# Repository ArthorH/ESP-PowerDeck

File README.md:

# ESP PowerDeck
Versitale development board for ESP32-S3 microcontroller

## Project Status: **Ongoing**  
**Design** ✅ — **Fabrication** ✅ — **Assembly** ✅ — **Bringup** ✅ — **Testing** ✅  
## Key technologies:
&nbsp;&nbsp;&nbsp;&nbsp; &nbsp;&nbsp;&nbsp;&nbsp; &nbsp;&nbsp;&nbsp;&nbsp; &nbsp;&nbsp;&nbsp;&nbsp;
## Who it's for

Want to play with robotics? Maybe you have a cool IoT project in mind? You don't want to hassle with assembling development modules or soldering jumper cables, and jump straight into controlling serious hardware—not just LEDs on a breadboard?

#### Power deck is for you! 
&nbsp;&nbsp;&nbsp;&nbsp; &nbsp;&nbsp;&nbsp;&nbsp;
# Features
- 60W Power delivery input
- High power 5V and 3.3V line outputs
- 3 Channel H-Bridge power output stage with "SafeMode" and to 43W single channel H-Bridge output
- I2C current feedback for H-Bridges
- WS2812 and servo otputs
- Built in UART bridge
- Built in USB 2.0 Hub for ESP32 OTG
- UVLO OVLO protection for barrel jack psu

# Block Diagram:

# Usage:
It can drive anything from simple DC motors and Steppers:

To driving bldc motors using advanced FOC alghoritms:

Also last but not least IoT projects are also possible:

# Layout:

# Author
Artem Horiunov
# License 
CERN-OHL-P V2

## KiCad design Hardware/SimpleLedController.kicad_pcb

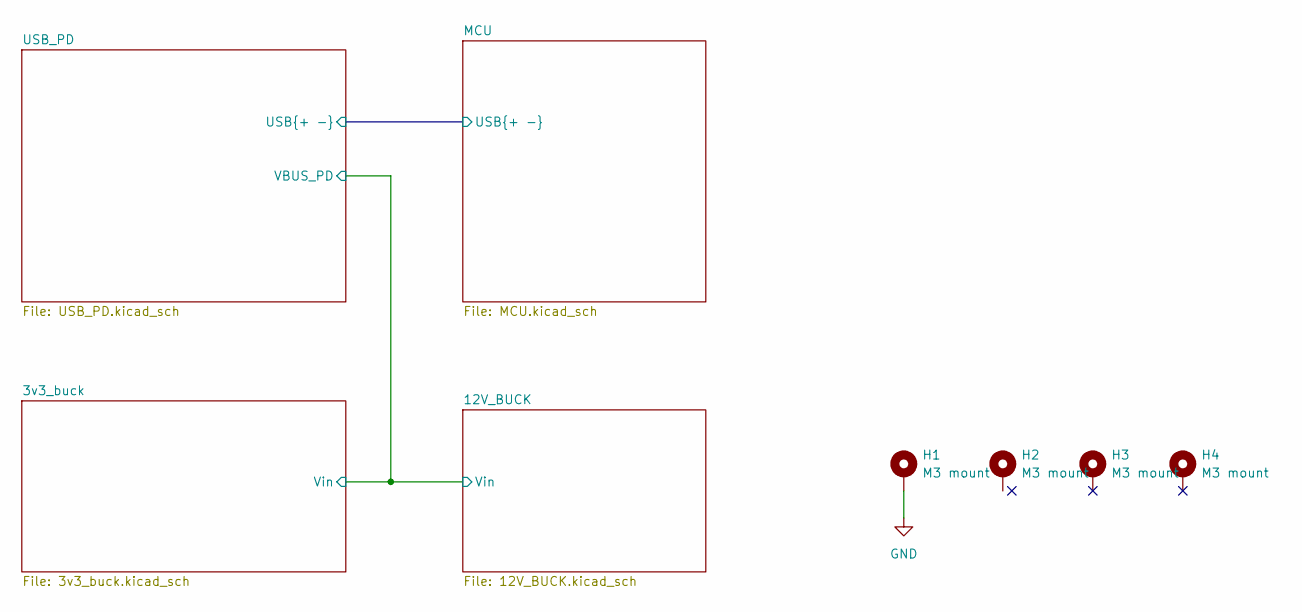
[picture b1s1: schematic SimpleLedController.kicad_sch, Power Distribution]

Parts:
H1, H2, H3, H4: M3 mount; MountingHole_3.2mm_M3_DIN965_Pad

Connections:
GND: H1.1; also elsewhere on the board

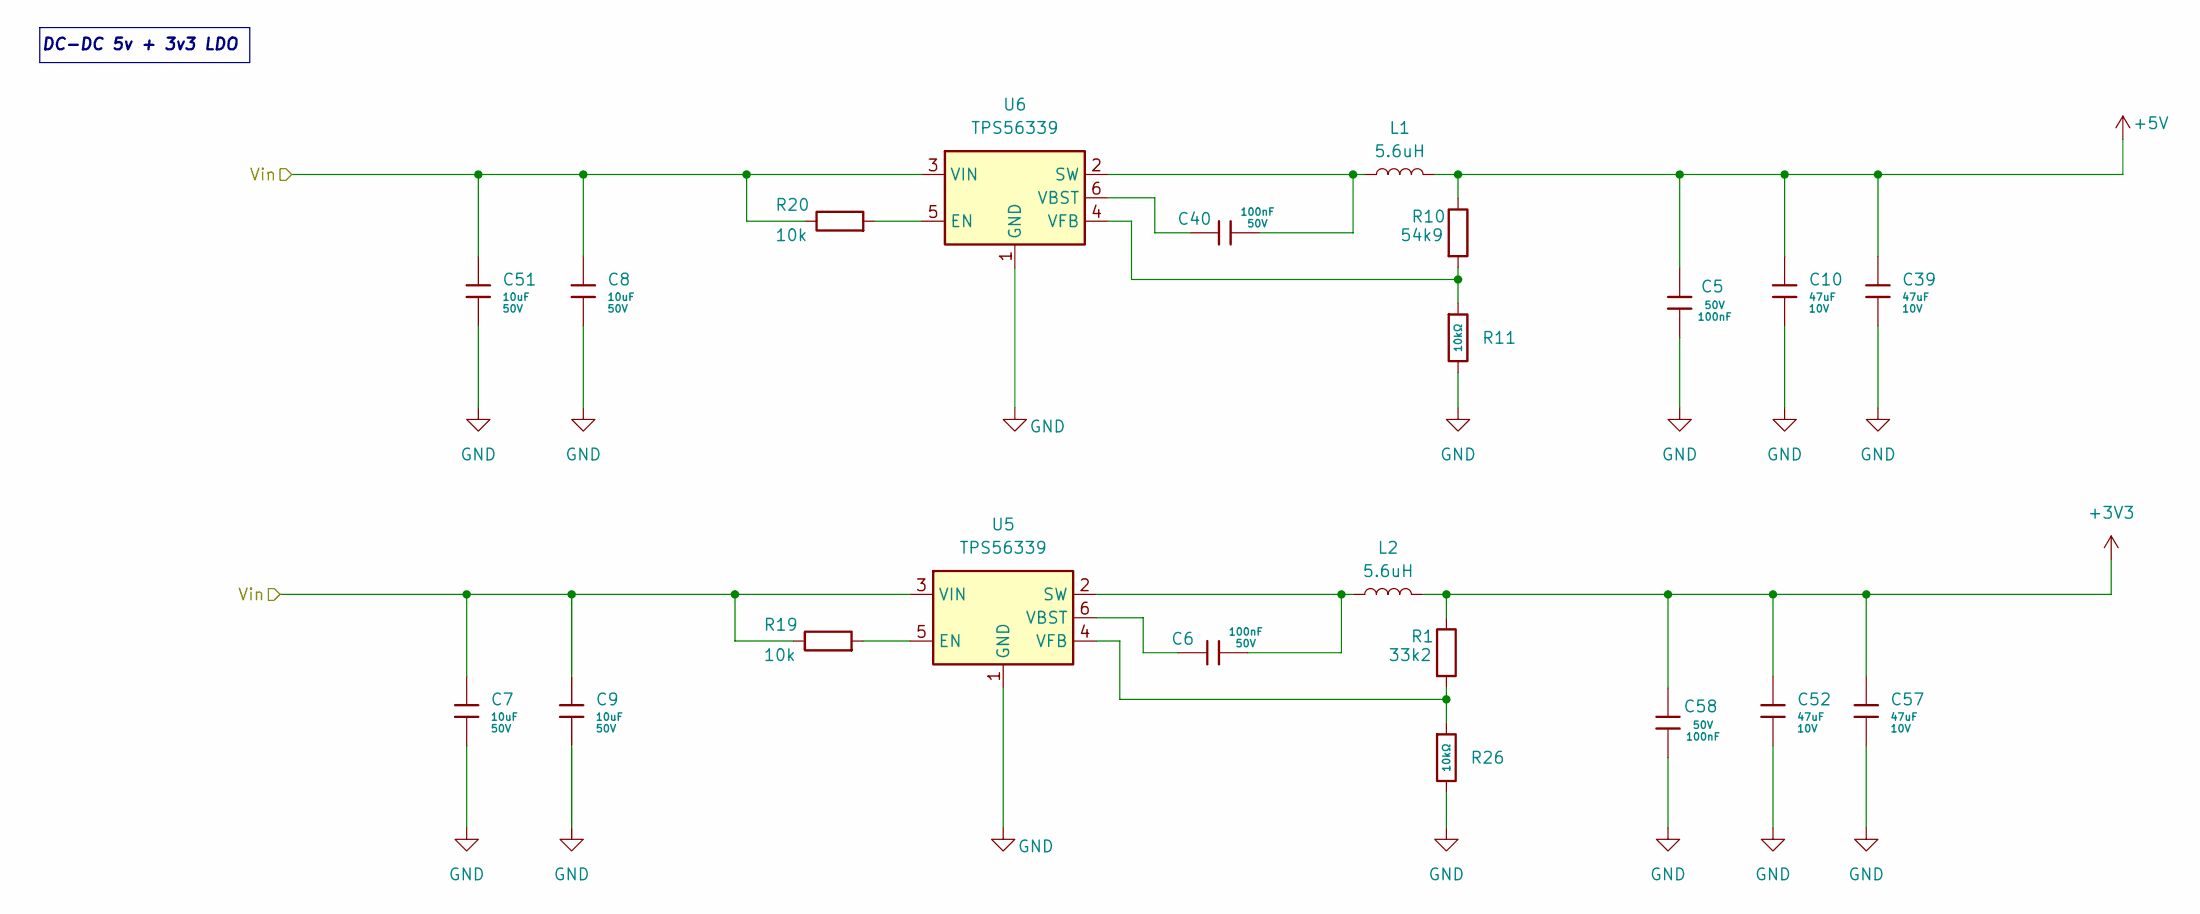
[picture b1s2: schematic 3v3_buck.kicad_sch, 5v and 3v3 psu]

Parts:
C5, C6, C40, C58: 100nF; C_0402; Voltage Rated 50V; Tolerance ±10%; Part CL05B104KB54PNC; LCSC C307331
C7, C8, C9, C51: 10uF; C_1206; Voltage Rated 50V; Tolerance ±10%; Part CL31A106KBHNNNE; LCSC C13585
C10, C39, C52, C57: 47uF; C_1206; Voltage Rated 10V; Tolerance ±20%; Part CL31A476MPHNNNE; LCSC C96123
L1, L2: 5.6uH; L_Sunlord_MWSA0518S
R1: 33k2; R_0402_1005Metric
R10: 54k9; R_0402_1005Metric
R11, R26: 10kΩ; R_0402; Overload Voltage (Max) 50V; Tolerance ±1%; Part 0402WGF1002TCE; LCSC C25744
R19, R20: 10k; R_0402_1005Metric
U5, U6: TPS56339; SOT-23-6

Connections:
+3V3: C52.1, C57.1, C58.2, L2.2, R1.1; also elsewhere on the board
+5V: C5.2, C10.1, C39.1, L1.2, R10.1; also elsewhere on the board
/USB_PD/VBUS: C7.1, C8.1, C9.1, C51.1, R19.1, R20.1, U5.3 (VIN), U6.3 (VIN); also elsewhere on the board
GND: C5.1, C7.2, C8.2, C9.2, C10.2, C39.2, C51.2, C52.2, C57.2, C58.1, R11.2, R26.2, U5.1 (GND), U6.1 (GND); also elsewhere on the board
unnamed: R19.2, U5.5 (EN)
unnamed: C6.2, L2.1, U5.2 (SW)
unnamed: C6.1, U5.6 (VBST)
unnamed: R1.2, R26.1, U5.4 (VFB)
unnamed: R20.2, U6.5 (EN)
unnamed: C40.2, L1.1, U6.2 (SW)
unnamed: C40.1, U6.6 (VBST)
unnamed: R10.2, R11.1, U6.4 (VFB)

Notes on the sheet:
DC-DC 5v + 3v3 LDO

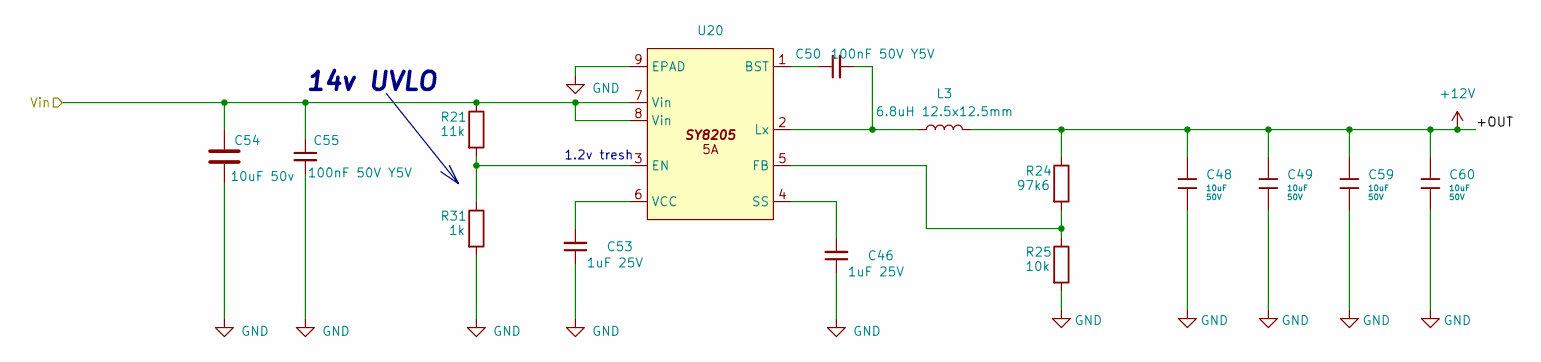
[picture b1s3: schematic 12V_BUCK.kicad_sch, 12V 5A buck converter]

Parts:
C46, C53: 1uF 25V; C_0402_1005Metric
C48, C49, C59, C60: 10uF; C_1206; Voltage Rated 50V; Tolerance ±10%; Part CL31A106KBHNNNE; LCSC C13585
C50, C55: 100nF 50V Y5V; C_0402_1005Metric
C54: 10uF 50v; C_0805_2012Metric
L3: 6.8uH 12.5x12.5mm; L_AVX_LMLP07A7; MPN YSPI0740-6R8M
R21: 11k; R_0402_1005Metric
R24: 97k6; R_0402_1005Metric
R25: 10k; R_0402_1005Metric
R31: 1k; R_0402_1005Metric
U20: Diodes_SO-8EP

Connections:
+12V: C48.1, C49.1, C59.1, C60.1, L3.2, R24.1; also elsewhere on the board
/USB_PD/VBUS: C54.1, C55.1, R21.1, U20.7 (Vin), U20.8 (Vin); also elsewhere on the board
GND: C46.1, C48.2, C49.2, C53.1, C54.2, C55.2, C59.2, C60.2, R25.2, R31.2, U20.9 (EPAD); also elsewhere on the board
unnamed: C50.1, U20.1 (BST)
unnamed: R21.2, R31.1, U20.3 (EN)
unnamed: R24.2, R25.1, U20.5 (FB)
unnamed: C50.2, L3.1, U20.2 (Lx)
unnamed: C46.2, U20.4 (SS)
unnamed: C53.2, U20.6 (VCC)

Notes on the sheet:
14v UVLO
1.2v tresh

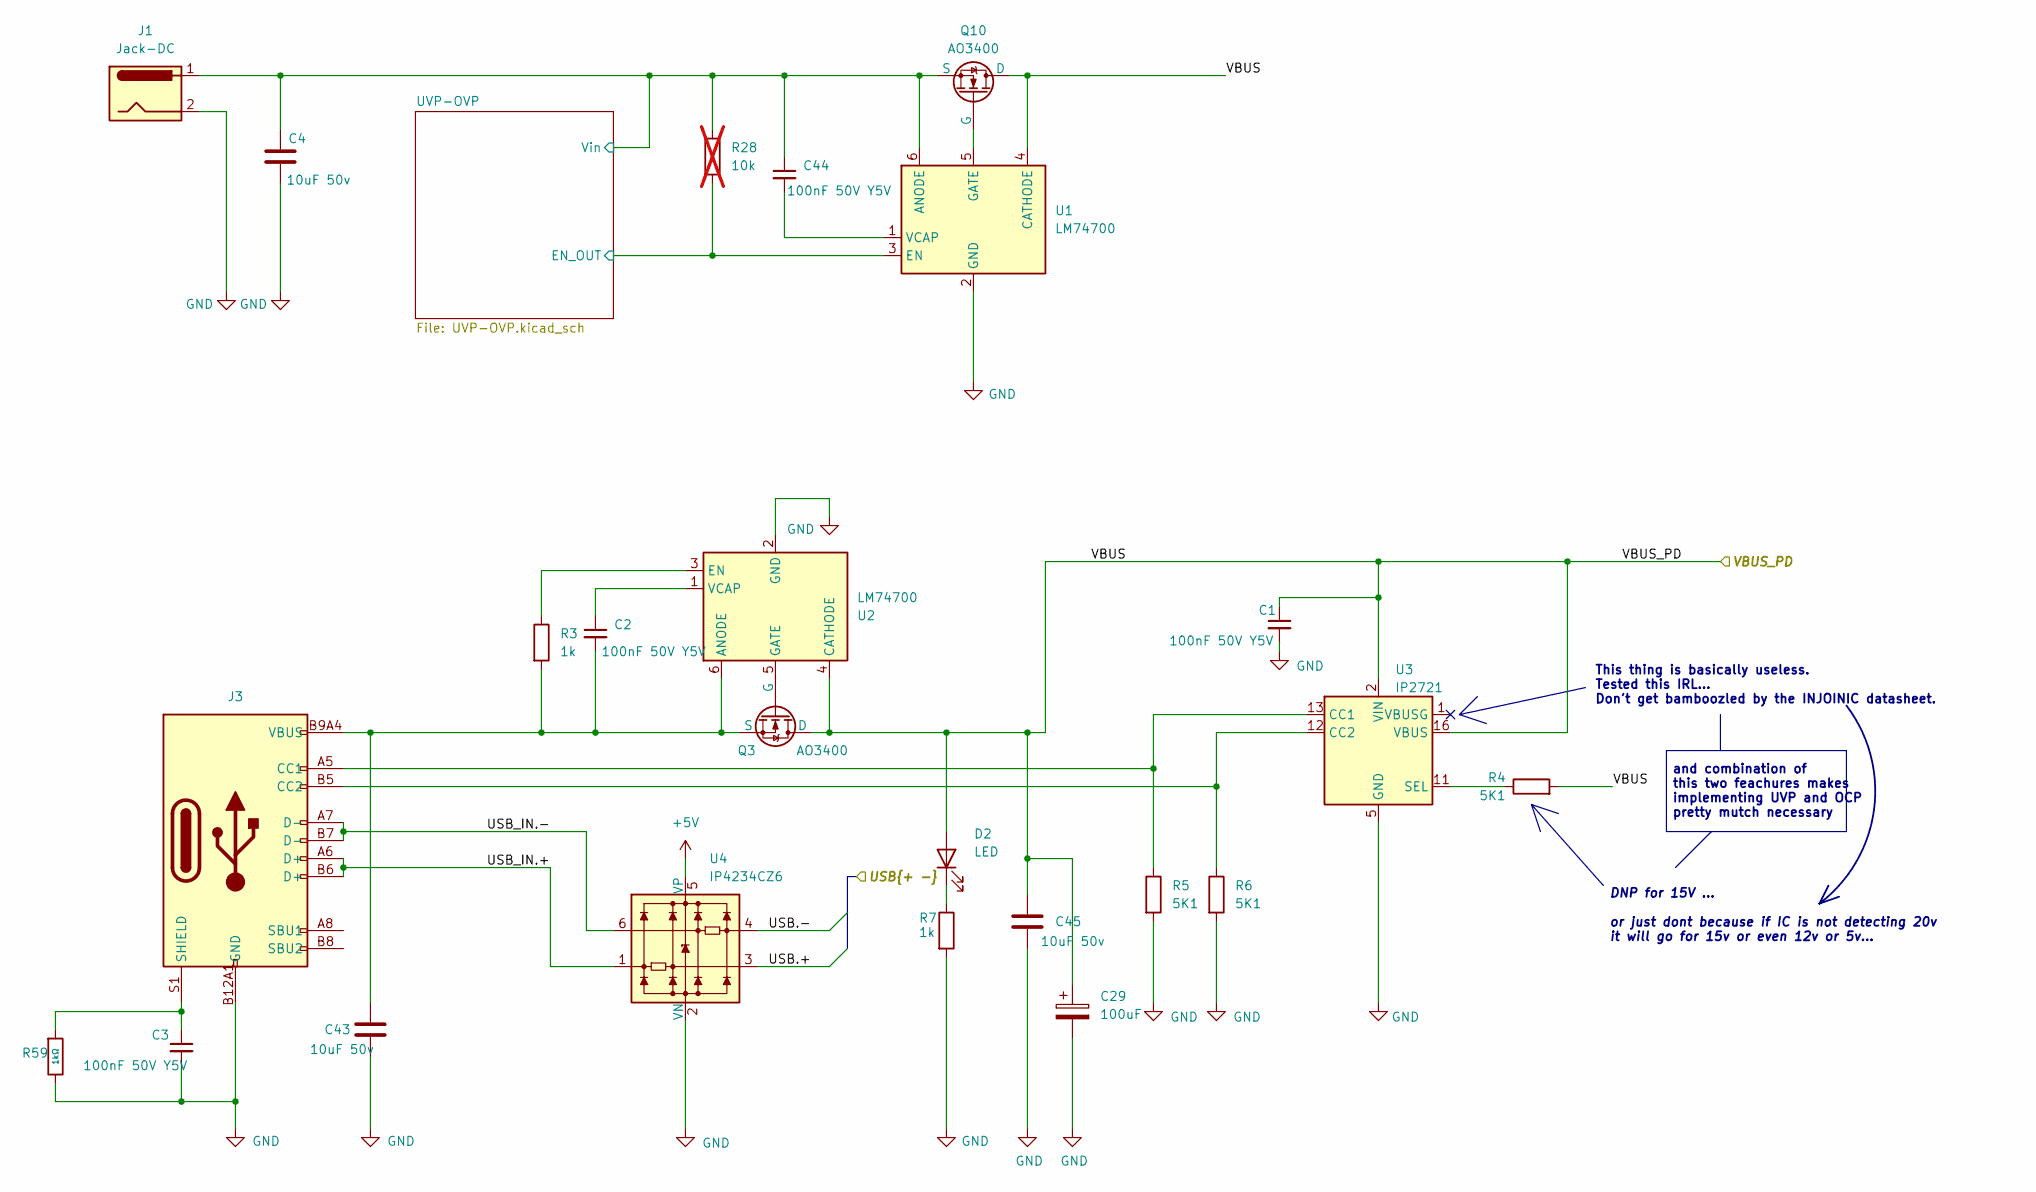
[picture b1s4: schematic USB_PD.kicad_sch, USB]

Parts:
C1, C2, C3, C44: 100nF 50V Y5V; C_0402_1005Metric
C4, C43, C45: 10uF 50v; C_0805_2012Metric
C29: 100uF; CP_Elec_6.3x5.4
D2: LED; D_0603_1608Metric
J1: Jack-DC; BarrelJack_Kycon_KLDX-0202-xC_Horizontal
J3: Connector, USB-TYPE-C-16P; TYPE-C-SMD_HX-TYPE-C-16PIN; LCSC C2927039
Q3, Q10: AO3400; SOT-23
R3, R7: 1k; R_0402_1005Metric
R4, R5, R6: 5K1; R_0402_1005Metric
R28: 10k; R_0402_1005Metric; not fitted
R59: 1kΩ; R_0402; Overload Voltage (Max) 50V; Tolerance ±1%; Part 0402WGF1001TCE; LCSC C11702
U1, U2: LM74700; SOT-23-6
U3: IP2721; TSSOP-16_4.4x5mm_P0.65mm
U4: IP4234CZ6; SC-74-6_1.55x2.9mm_P0.95mm

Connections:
+5V: U4.5 (VP); also elsewhere on the board
/MCU/USB.+: U4.3; also elsewhere on the board
/MCU/USB.-: U4.4; also elsewhere on the board
/USB_PD/USB_IN.+: J3.A6 (D+), J3.B6 (D+), U4.1
/USB_PD/USB_IN.-: J3.A7 (D-), J3.B7 (D-), U4.6
/USB_PD/UVP-OVP/EN_OUT: R28.2, U1.3 (EN); also elsewhere on the board
/USB_PD/UVP-OVP/Vin: C4.1, C44.1, J1.1, Q10.3 (S), R28.1, U1.6 (ANODE); also elsewhere on the board
/USB_PD/VBUS: C1.1, C29.1, C45.1, D2.2 (A), Q3.2 (D), Q10.2 (D), R4.2, U1.4 (CATHODE), U2.4 (CATHODE), U3.2 (VIN), U3.16 (VBUS); also elsewhere on the board
GND: C1.2, C3.2, C4.2, C29.2, C43.2, C45.2, J1.2, J3.A12B1 (GND), J3.B12A1 (GND), R5.2, R6.2, R7.2, R59.2, U1.2 (GND), U2.2 (GND), U3.5 (GND), U4.2 (VN); also elsewhere on the board
unnamed: D2.1 (K), R7.1
unnamed: J3.A5 (CC1), R5.1, U3.13 (CC1)
unnamed: J3.B5 (CC2), R6.1, U3.12 (CC2)
unnamed: C3.1, J3.S1 (SHIELD), R59.1
unnamed: Q3.1 (G), U2.5 (GATE)
unnamed: C2.2, C43.1, J3.A9B4 (VBUS), J3.B9A4 (VBUS), Q3.3 (S), R3.2, U2.6 (ANODE)
unnamed: Q10.1 (G), U1.5 (GATE)
unnamed: C44.2, U1.1 (VCAP)
unnamed: R3.1, U2.3 (EN)
unnamed: C2.1, U2.1 (VCAP)
unnamed: R4.1, U3.11 (SEL)

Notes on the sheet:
and combination of this two feachures makes implementing UVP and OCP pretty mutch necessary
DNP for 15V ... or just dont because if IC is not detecting 20v it will go for 15v or even 12v or 5v...
This thing is basically useless. Tested this IRL... Don't get bamboozled by the INJOINIC datasheet.

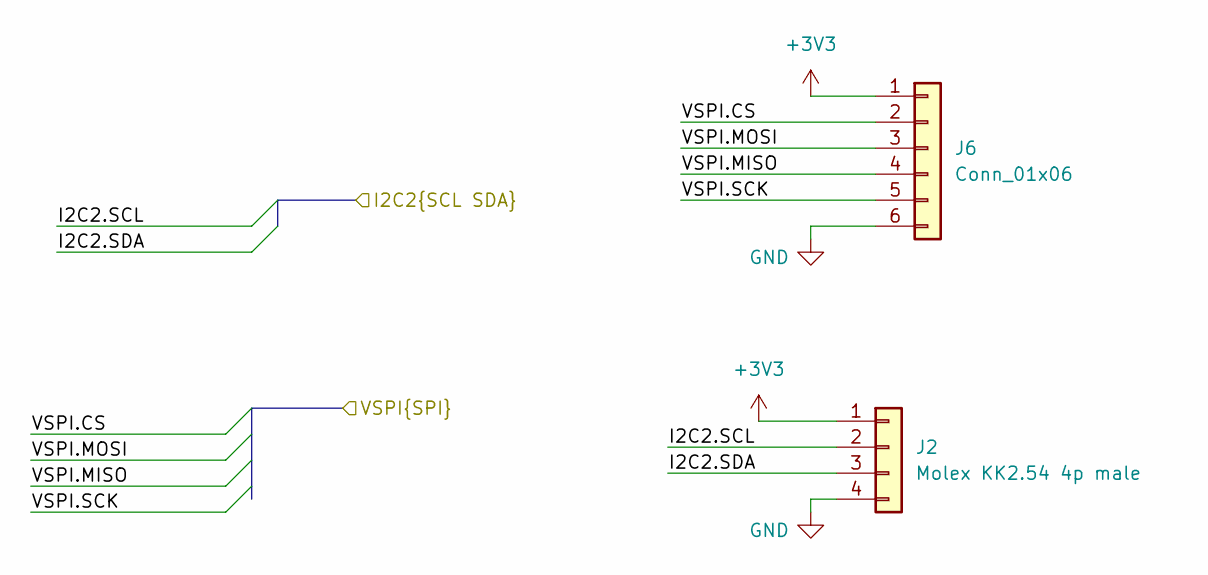
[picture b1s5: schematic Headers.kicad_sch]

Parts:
J2: Molex KK2.54 4p male; JST_GH_BM04B-GHS-TBT_1x04-1MP_P1.25mm_Vertical
J6: Conn_01x06; JST_GH_BM06B-GHS-TBT_1x06-1MP_P1.25mm_Vertical

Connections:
+3V3: J2.1, J6.1; also elsewhere on the board
/MCU/ESP32S3/I2C2.SCL: J2.2; also elsewhere on the board
/MCU/ESP32S3/I2C2.SDA: J2.3; also elsewhere on the board
/MCU/ESP32S3/VSPI.CS: J6.2; also elsewhere on the board
/MCU/ESP32S3/VSPI.MISO: J6.4; also elsewhere on the board
/MCU/ESP32S3/VSPI.MOSI: J6.3; also elsewhere on the board
/MCU/ESP32S3/VSPI.SCK: J6.5; also elsewhere on the board
GND: J2.4, J6.6; also elsewhere on the board

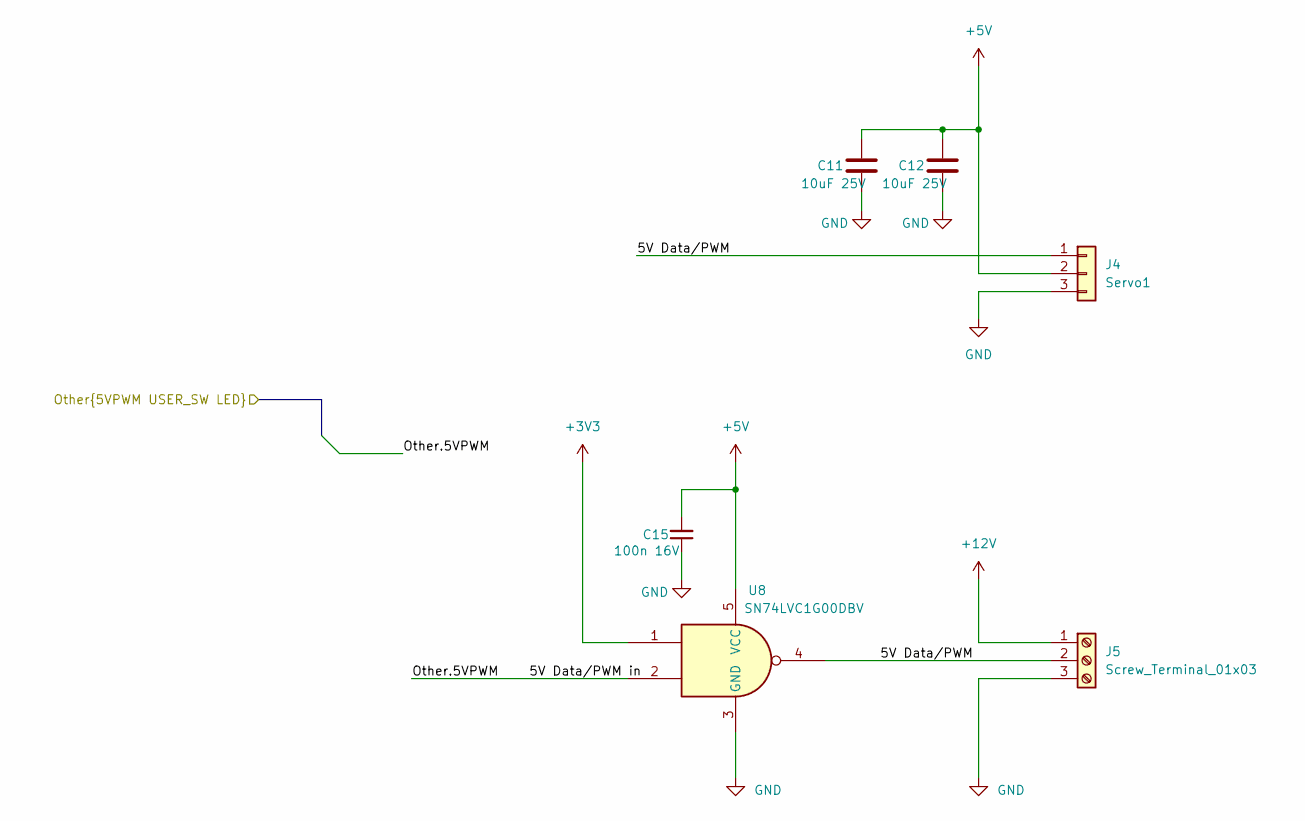
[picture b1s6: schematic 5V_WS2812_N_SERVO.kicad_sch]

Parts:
C11, C12: 10uF 25V; R_0402_1005Metric
C15: 100n 16V; C_0402_1005Metric
J4: Servo1; PinHeader_1x03_P2.54mm_Vertical_SMD_Pin1Left
J5: Screw_Terminal_01x03; TerminalBlock_Altech_AK300-3_P5.00mm
U8: SN74LVC1G00DBV; SOT-23-5

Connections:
+3V3: U8.1; also elsewhere on the board
+5V: C11.1, C12.1, C15.2, J4.2, U8.5 (VCC); also elsewhere on the board
+12V: J5.1; also elsewhere on the board
/MCU/5V WS2812 and Servo/5V Data/PWM: J4.1, J5.2, U8.4
/MCU/5V WS2812 and Servo/Other.5VPWM: U8.2; also elsewhere on the board
GND: C11.2, C12.2, C15.1, J4.3, J5.3, U8.3 (GND); also elsewhere on the board

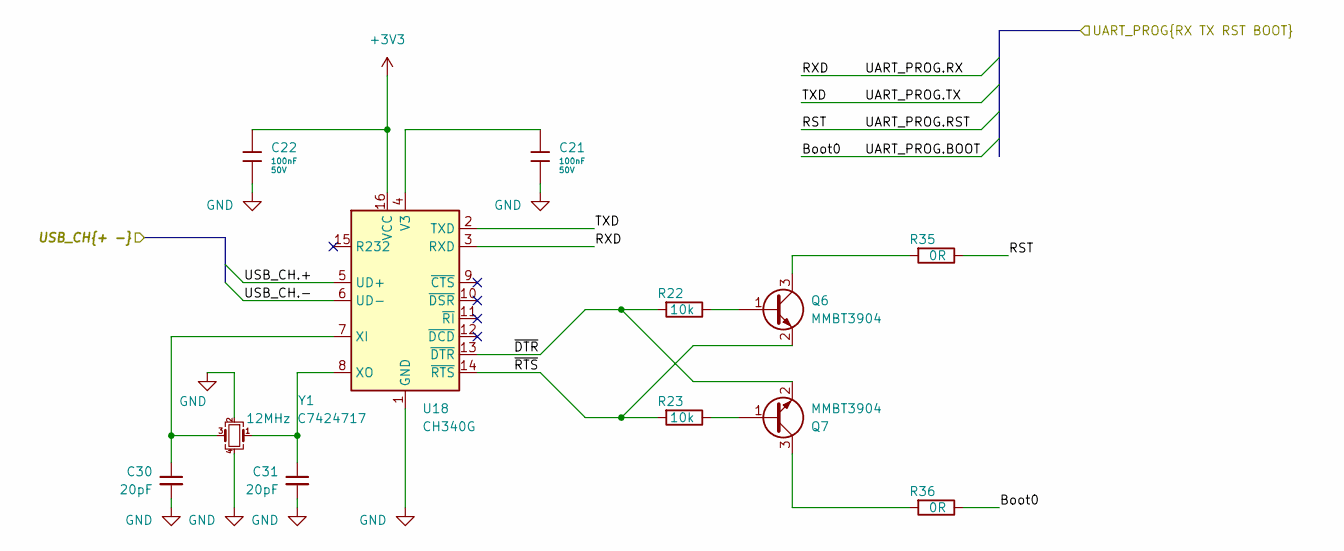
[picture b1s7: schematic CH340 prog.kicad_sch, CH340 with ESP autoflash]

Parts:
C21, C22: 100nF; C_0402; Voltage Rated 50V; Tolerance ±10%; Part CL05B104KB54PNC; LCSC C307331
C30, C31: 20pF; C_0402_1005Metric
Q6, Q7: MMBT3904; SOT-23
R22, R23: 10k; R_0402_1005Metric
R35, R36: 0R; R_0402_1005Metric
U18: CH340G; SOIC-16_3.9x9.9mm_P1.27mm
Y1: 12MHz C7424717; Crystal_SMD_3225-4Pin_3.2x2.5mm

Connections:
+3V3: C22.1, U18.16 (VCC); also elsewhere on the board
/MCU/CH340 prog/UART_PROG.BOOT: R36.1; also elsewhere on the board
/MCU/CH340 prog/UART_PROG.RST: R35.1; also elsewhere on the board
/MCU/CH340 prog/UART_PROG.RX: U18.3 (RXD); also elsewhere on the board
/MCU/CH340 prog/UART_PROG.TX: U18.2 (TXD); also elsewhere on the board
/MCU/CH340 prog/USB_CH.+: U18.5 (UD+); also elsewhere on the board
/MCU/CH340 prog/USB_CH.-: U18.6 (UD-); also elsewhere on the board
/MCU/CH340 prog/~DTR: Q7.2 (E), R22.2, U18.13 (~DTR)
/MCU/CH340 prog/~RTS: Q6.2 (E), R23.2, U18.14 (~RTS)
GND: C21.2, C22.2, C30.2, C31.2, U18.1 (GND), Y1.2, Y1.4; also elsewhere on the board
unnamed: Q6.1 (B), R22.1
unnamed: Q6.3 (C), R35.2
unnamed: Q7.1 (B), R23.1
unnamed: Q7.3 (C), R36.2
unnamed: C21.1, U18.4 (V3)
unnamed: C30.1, U18.7 (XI), Y1.3
unnamed: C31.1, U18.8 (XO), Y1.1

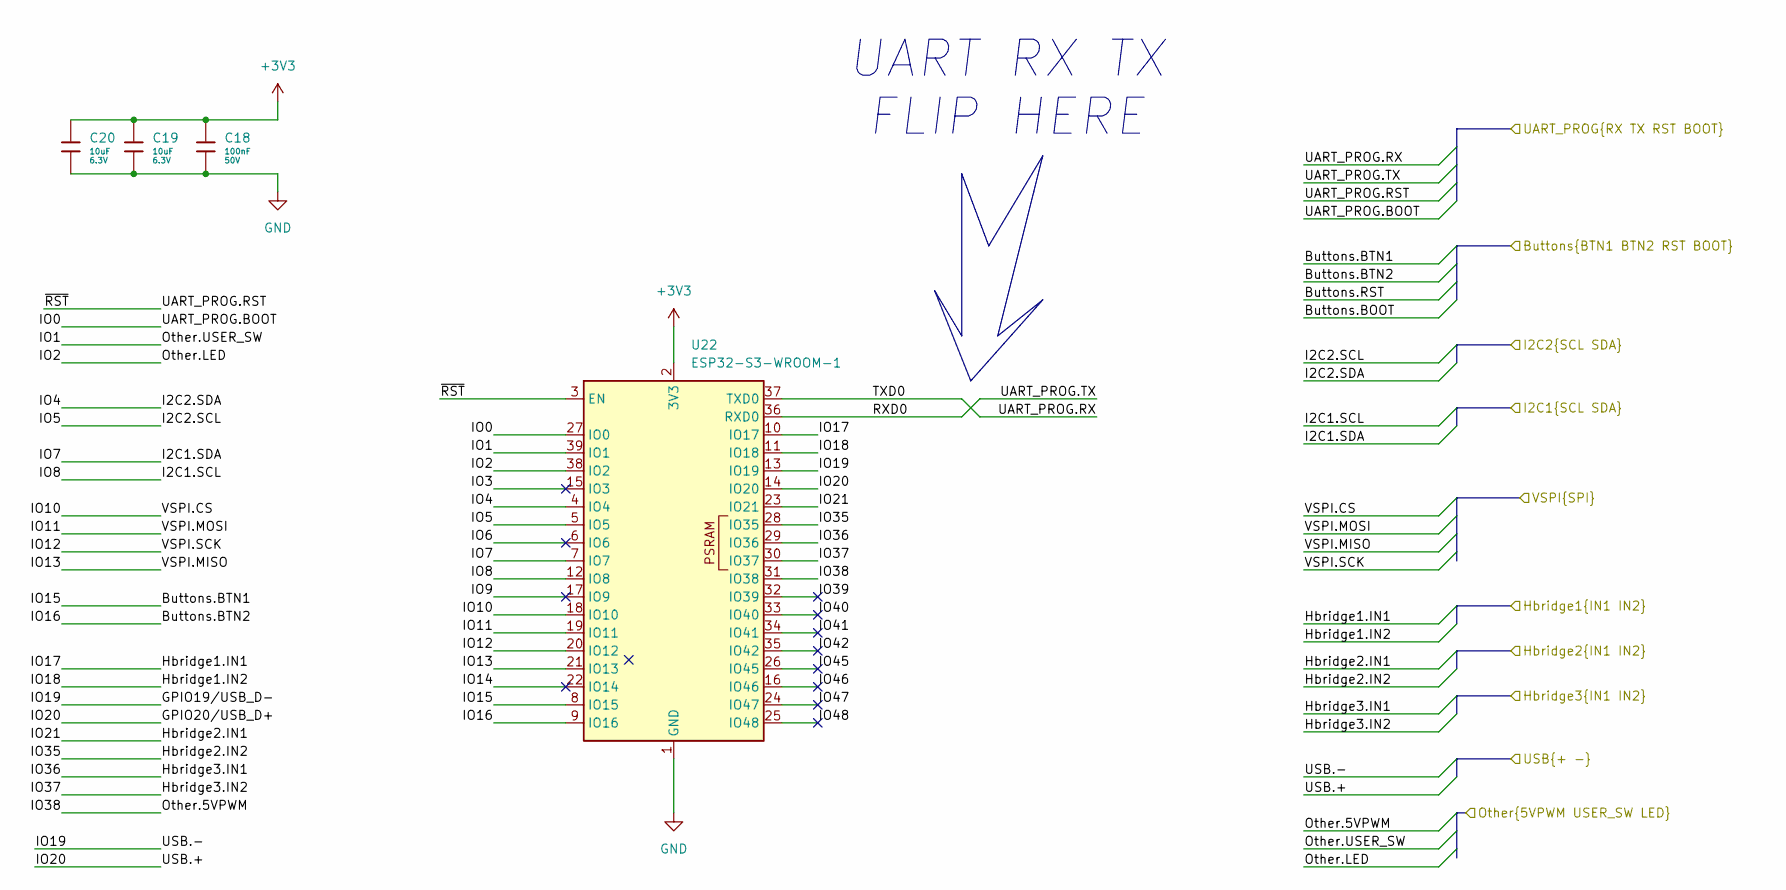
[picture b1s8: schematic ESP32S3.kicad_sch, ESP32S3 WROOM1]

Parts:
C18: 100nF; C_0402; Voltage Rated 50V; Tolerance ±10%; Part CL05B104KB54PNC; LCSC C307331
C19, C20: 10uF; C_0402; Voltage Rated 6.3V; Tolerance ±20%; Part CL05A106MQ5NUNC; LCSC C15525
U22: ESP32-S3-WROOM-1

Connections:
+3V3: C18.1, C19.1, C20.1, U22.2 (3V3); also elsewhere on the board
/MCU/5V WS2812 and Servo/Other.5VPWM: U22.31 (IO38); also elsewhere on the board
/MCU/5V WS2812 and Servo/Other.LED: U22.38 (IO2); also elsewhere on the board
/MCU/5V WS2812 and Servo/Other.USER_SW: U22.39 (IO1); also elsewhere on the board
/MCU/Buttons/Buttons.BTN1: U22.8 (IO15); also elsewhere on the board
/MCU/Buttons/Buttons.BTN2: U22.9 (IO16)
/MCU/CH340 prog/UART_PROG.BOOT: U22.27 (IO0); also elsewhere on the board
/MCU/CH340 prog/UART_PROG.RST: U22.3 (EN); also elsewhere on the board
/MCU/CH340 prog/UART_PROG.RX: U22.37 (TXD0); also elsewhere on the board
/MCU/CH340 prog/UART_PROG.TX: U22.36 (RXD0); also elsewhere on the board
/MCU/ESP32S3/Hbridge1.IN1: U22.10 (IO17); also elsewhere on the board
/MCU/ESP32S3/Hbridge1.IN2: U22.11 (IO18); also elsewhere on the board
/MCU/ESP32S3/Hbridge2.IN1: U22.23 (IO21); also elsewhere on the board
/MCU/ESP32S3/Hbridge2.IN2: U22.28 (IO35); also elsewhere on the board
/MCU/ESP32S3/Hbridge3.IN1: U22.29 (IO36); also elsewhere on the board
/MCU/ESP32S3/Hbridge3.IN2: U22.30 (IO37); also elsewhere on the board
/MCU/ESP32S3/I2C1.SCL: U22.12 (IO8); also elsewhere on the board
/MCU/ESP32S3/I2C1.SDA: U22.7 (IO7); also elsewhere on the board
/MCU/ESP32S3/I2C2.SCL: U22.5 (IO5); also elsewhere on the board
/MCU/ESP32S3/I2C2.SDA: U22.4 (IO4); also elsewhere on the board
/MCU/ESP32S3/IO3: U22.15 (IO3)
/MCU/ESP32S3/IO6: U22.6 (IO6)
/MCU/ESP32S3/IO9: U22.17 (IO9)
/MCU/ESP32S3/IO14: U22.22 (IO14)
/MCU/ESP32S3/IO39: U22.32 (IO39)
/MCU/ESP32S3/IO40: U22.33 (IO40)
/MCU/ESP32S3/IO41: U22.34 (IO41)
/MCU/ESP32S3/IO42: U22.35 (IO42)
/MCU/ESP32S3/IO45: U22.26 (IO45)
/MCU/ESP32S3/IO46: U22.16 (IO46)
/MCU/ESP32S3/IO47: U22.24 (IO47)
/MCU/ESP32S3/IO48: U22.25 (IO48)
/MCU/ESP32S3/USB.+: U22.14 (IO20); also elsewhere on the board
/MCU/ESP32S3/USB.-: U22.13 (IO19); also elsewhere on the board
/MCU/ESP32S3/VSPI.CS: U22.18 (IO10); also elsewhere on the board
/MCU/ESP32S3/VSPI.MISO: U22.21 (IO13); also elsewhere on the board
/MCU/ESP32S3/VSPI.MOSI: U22.19 (IO11); also elsewhere on the board
/MCU/ESP32S3/VSPI.SCK: U22.20 (IO12); also elsewhere on the board
GND: C18.2, C19.2, C20.2, U22.1 (GND), U22.40 (GND), U22.41 (GND); also elsewhere on the board

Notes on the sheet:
UART RX TX FLIP HERE

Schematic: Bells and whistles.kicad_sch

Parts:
D3: Red; D_0603; Part KT-0603R; LCSC C2286
R8: 1kΩ; R_0402; Overload Voltage (Max) 50V; Tolerance ±1%; Part 0402WGF1001TCE; LCSC C11702

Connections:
/MCU/5V WS2812 and Servo/Other.LED: D3.2; also elsewhere on the board
GND: R8.2; also elsewhere on the board
unnamed: D3.1, R8.1

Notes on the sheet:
buzz with PWM on engines if you will
buzzer is no more

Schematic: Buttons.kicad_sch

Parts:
C13, C16, C17: 100n 16V; C_0402_1005Metric
R9, R15, R16: 10k; R_0402_1005Metric
R13, R17, R18: 100R; R_0402_1005Metric
SW1, SW3, SW4: RESET; SW_Tactile_SPST_NO_Straight_CK_PTS636Sx25SMTRLFS; MPN TSB008A2530A; LCSC C2888954

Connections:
+3V3: R9.1, R15.1, R16.1; also elsewhere on the board
/MCU/Buttons/Buttons.BOOT: C16.2, R15.2, R17.1
/MCU/Buttons/Buttons.BTN1: C13.2, R9.2, R13.1; also elsewhere on the board
/MCU/Buttons/Buttons.RST: C17.2, R16.2, R18.1
GND: C13.1, C16.1, C17.1, SW1.2, SW3.2, SW4.2; also elsewhere on the board
unnamed: R13.2, SW1.1
unnamed: R17.2, SW3.1
unnamed: R18.2, SW4.1

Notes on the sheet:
USER button2 is no more use WIFI :)
Note: if autoflash works as intended then remove boot 1 and replace as user btn

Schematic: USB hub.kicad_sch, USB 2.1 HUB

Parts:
C32, C33: 10uF 6.3V; C_0603_1608Metric
U19: SL2.1A; SO-16_3.9x9.9mm_P1.27mm
Y2: 12MHz C7424717; Crystal_SMD_3225-4Pin_3.2x2.5mm

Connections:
+5V: U19.11 (VDD5); also elsewhere on the board
/MCU/CH340 prog/USB_CH.+: U19.8 (DP1); also elsewhere on the board
/MCU/CH340 prog/USB_CH.-: U19.7 (DM1); also elsewhere on the board
/MCU/ESP32S3/USB.+: U19.6 (DP2); also elsewhere on the board
/MCU/ESP32S3/USB.-: U19.5 (DM2); also elsewhere on the board
/MCU/USB.+: U19.10 (DP); also elsewhere on the board
/MCU/USB.-: U19.9 (DM); also elsewhere on the board
GND: C32.1, C33.1, U19.12 (GND), Y2.2, Y2.4; also elsewhere on the board
unnamed: C32.2, U19.14 (VDD18)
unnamed: C33.2, U19.13 (VDD33)
unnamed: U19.16 (XIN), Y2.3
unnamed: U19.15 (XOUT), Y2.1

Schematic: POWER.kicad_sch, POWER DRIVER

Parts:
D1: LED; LED_0603_1608Metric
R12: 10kΩ; R_0402; Overload Voltage (Max) 50V; Tolerance ±1%; Part 0402WGF1002TCE; LCSC C25744
R47: 10k; R_0402_1005Metric
R48: 680R; R_0402_1005Metric
S1: DIP Switch x 2; SW-SMD_218-2LPSTRF; Current Rating 25mA; Voltage Rating 24V; Part 218-2LPSTR; LCSC C2961921

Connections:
+3V3: S1.3, S1.4; also elsewhere on the board
/MCU/5V WS2812 and Servo/Other.USER_SW: R12.1, S1.1; also elsewhere on the board
/MCU/POWER SECTION/DRV1/~SAFE OPERATION: D1.2 (A), R47.1, S1.2; also elsewhere on the board
GND: R12.2, R47.2, R48.2; also elsewhere on the board
unnamed: D1.1 (K), R48.1

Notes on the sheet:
SAFE MODE OFF

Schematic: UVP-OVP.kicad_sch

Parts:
D4: 14v; D_SOD-123
Q4: MMBT3906; SOT-23
Q5, Q9: MMBT3904; SOT-23
R39: 1k5; R_0402_1005Metric
R40: 39k; R_0402_1005Metric
R41, R42, R43: 10k; R_0402_1005Metric
R44: 1k; R_0402_1005Metric

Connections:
/USB_PD/UVP-OVP/EN_OUT: Q4.3 (C), R43.1; also elsewhere on the board
/USB_PD/UVP-OVP/Vin: R39.1, R40.1, R41.1; also elsewhere on the board
GND: D4.2 (A), Q9.2 (E), R43.2, R44.2; also elsewhere on the board
unnamed: D4.1 (K), Q5.2 (E)
unnamed: Q4.1 (B), R42.1
unnamed: Q4.2 (E), R39.2
unnamed: Q5.1 (B), Q9.3 (C), R41.2
unnamed: Q5.3 (C), R42.2
unnamed: Q9.1 (B), R40.2, R44.1

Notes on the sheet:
BRAND NEW!
Artem H
3 transistor all-in-one OVP UVP

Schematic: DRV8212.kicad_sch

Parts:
C23, C26: 100nF; C_0402; Voltage Rated 50V; Tolerance ±10%; Part CL05B104KB54PNC; LCSC C307331
C79: 100uF; CP_Elec_6.3x5.4
C80: 100nF; C_0402_1005Metric
C81, C82, C83: 100n 16V; C_0402_1005Metric
J12: Screw_Terminal_01x02; TerminalBlock_Altech_AK300-2_P5.00mm
R2, R30, R53, R54: 0Ω; R_0402; Overload Voltage (Max) 50V; Tolerance ±1%; Part 0402WGF0000TCE; LCSC C17168; not fitted
R34, R45: 10Ω; R_0402; Overload Voltage (Max) 50V; Tolerance ±1%; Part 0402WGF100JTCE; LCSC C25077
R50: R010; R_0805; Overload Voltage (Max) 150V; Tolerance ±1%; Part 0805W8F200KT5E; LCSC C163089
U7: INA219AxDCN; SOT-23-8
U24: DRV8870DDA; Texas_HTSOP-8-1EP_3.9x4.9mm_P1.27mm_EP2.95x4.9mm_Mask2.4x3.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
U25, U26: SN74LVC1G00DBV; SOT-23-5

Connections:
+3V3: C23.1, C81.2, C82.2, C83.2, R53.1, R54.1, U7.4 (VS), U24.4 (VREF), U25.5 (VCC), U26.5 (VCC); also elsewhere on the board
+12V: C79.1, C80.2, U24.5 (VM); also elsewhere on the board
/MCU/ESP32S3/Hbridge3.IN1: U24.3 (IN1); also elsewhere on the board
/MCU/ESP32S3/Hbridge3.IN2: U25.1; also elsewhere on the board
/MCU/ESP32S3/I2C1.SCL: U7.5 (SCL); also elsewhere on the board
/MCU/ESP32S3/I2C1.SDA: U7.6 (SDA); also elsewhere on the board
/MCU/POWER SECTION/DRV1/~SAFE OPERATION: U25.2; also elsewhere on the board
/MCU/POWER SECTION/DRV3/IN22: U24.2 (IN2), U26.4
GND: C23.2, C79.2, C80.1, C81.1, C82.1, C83.1, R2.2, R30.2, R45.2, R50.2, U7.3 (GND), U24.1 (GND), U24.9 (GND), U25.3 (GND), U26.3 (GND); also elsewhere on the board
unnamed: J12.1, U24.6 (OUT1)
unnamed: J12.2, U24.8 (OUT2)
unnamed: R2.1, R54.2, U7.7 (A0)
unnamed: R30.1, R53.2, U7.8 (A1)
unnamed: C26.1, R34.1, U7.1 (IN+)
unnamed: C26.2, R45.1, U7.2 (IN-)
unnamed: R34.2, R50.1, U24.7 (ISEN)
unnamed: U25.4, U26.1, U26.2

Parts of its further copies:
C24, C25, C27, C28: 100nF; C_0402; Voltage Rated 50V; Tolerance ±10%; Part CL05B104KB54PNC; LCSC C307331
C84, C89: 100uF; CP_Elec_6.3x5.4
C86, C87, C88, C91, C92, C93: 100n 16V; C_0402_1005Metric
J13, J14: Screw_Terminal_01x02; TerminalBlock_Altech_AK300-2_P5.00mm
R27, R29, R32, R33, R55, R56, R57, R58: 0Ω; R_0402; Overload Voltage (Max) 50V; Tolerance ±1%; Part 0402WGF0000TCE; LCSC C17168; not fitted
R37, R38, R46, R49: 10Ω; R_0402; Overload Voltage (Max) 50V; Tolerance ±1%; Part 0402WGF100JTCE; LCSC C25077
R51, R52: R010; R_0805; Overload Voltage (Max) 150V; Tolerance ±1%; Part 0805W8F200KT5E; LCSC C163089
U9, U10: INA219AxDCN; SOT-23-8
U27, U30: DRV8870DDA; Texas_HTSOP-8-1EP_3.9x4.9mm_P1.27mm_EP2.95x4.9mm_Mask2.4x3.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
U28, U29, U31, U32: SN74LVC1G00DBV; SOT-23-5

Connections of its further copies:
+3V3: C24.1, C25.1, C86.2, C87.2, C88.2, C91.2, C92.2, C93.2, R55.1, R56.1, R57.1, R58.1, U9.4 (VS), U10.4 (VS), U27.4 (VREF), U28.5 (VCC), U29.5 (VCC), U30.4 (VREF), U31.5 (VCC), U32.5 (VCC); also elsewhere on the board
+12V: C84.1, C89.1, U27.5 (VM), U30.5 (VM); also elsewhere on the board
/MCU/ESP32S3/Hbridge1.IN1: U27.3 (IN1); also elsewhere on the board
/MCU/ESP32S3/Hbridge1.IN2: U28.1; also elsewhere on the board
/MCU/ESP32S3/Hbridge2.IN1: U30.3 (IN1); also elsewhere on the board
/MCU/ESP32S3/Hbridge2.IN2: U31.1; also elsewhere on the board
/MCU/ESP32S3/I2C1.SCL: U9.5 (SCL), U10.5 (SCL); also elsewhere on the board
/MCU/ESP32S3/I2C1.SDA: U9.6 (SDA), U10.6 (SDA); also elsewhere on the board
/MCU/POWER SECTION/DRV1/IN22: U27.2 (IN2), U29.4
/MCU/POWER SECTION/DRV1/~SAFE OPERATION: U28.2, U31.2; also elsewhere on the board
/MCU/POWER SECTION/DRV2/IN22: U30.2 (IN2), U32.4
GND: C24.2, C25.2, C84.2, C86.1, C87.1, C88.1, C89.2, C91.1, C92.1, C93.1, R27.2, R29.2, R32.2, R33.2, R46.2, R49.2, R51.2, R52.2, U9.3 (GND), U10.3 (GND), U27.1 (GND), U27.9 (GND), U28.3 (GND), U29.3 (GND), U30.1 (GND), U30.9 (GND), U31.3 (GND), U32.3 (GND); also elsewhere on the board
unnamed: J13.1, U27.6 (OUT1)
unnamed: J13.2, U27.8 (OUT2)
unnamed: J14.1, U30.6 (OUT1)
unnamed: J14.2, U30.8 (OUT2)
unnamed: R27.1, R56.2, U9.7 (A0)
unnamed: R32.1, R55.2, U9.8 (A1)
unnamed: C27.1, R37.1, U9.1 (IN+)
unnamed: C27.2, R46.1, U9.2 (IN-)
unnamed: R29.1, R58.2, U10.7 (A0)
unnamed: R33.1, R57.2, U10.8 (A1)
unnamed: C28.1, R38.1, U10.1 (IN+)
unnamed: C28.2, R49.1, U10.2 (IN-)
unnamed: R37.2, R51.1, U27.7 (ISEN)
unnamed: U28.4, U29.1, U29.2
unnamed: R38.2, R52.1, U30.7 (ISEN)
unnamed: U31.4, U32.1, U32.2

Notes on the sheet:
expecting up to 6A
NOTE: Safe mode prevents user from shorting h-bridge VCC to GND while using RGB led strip. It effectively switches h-bridge to half bridge so only IN1 could be operated
FVM025ADA101M0654
0.010R (60mOhm) with 0.2W power package
40mV full scale
Polarity in safe mode operation

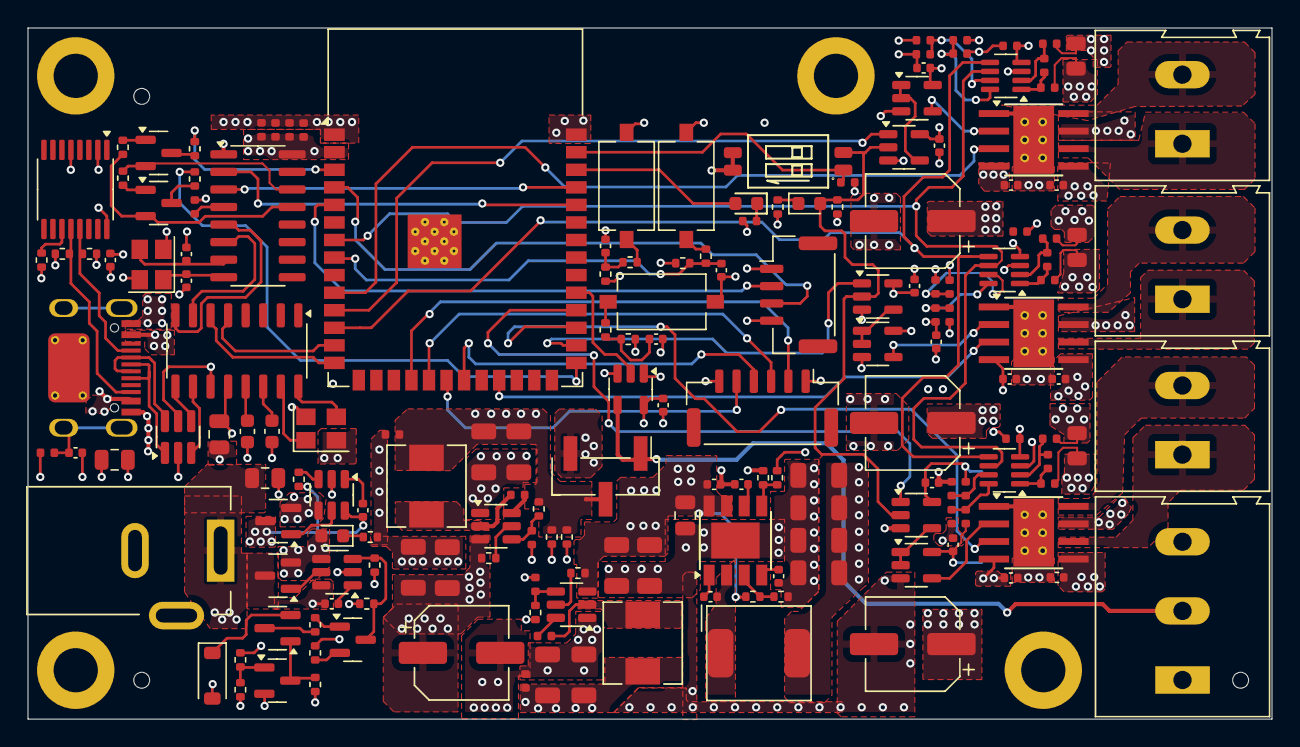
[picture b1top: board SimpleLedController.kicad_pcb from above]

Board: 4 copper layers, 90.0 x 50.0 mm, 179 parts (0 on the bottom side), 117 nets.

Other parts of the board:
C85, C90: 1uF 16V; C_0402_1005Metric

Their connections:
+12V: C85.2, C90.2; also elsewhere on the board
GND: C85.1, C90.1; also elsewhere on the board

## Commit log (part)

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2025-02-08 Finish Schematic and component placement
2025-02-08 Pack to hardware folder
2025-02-10 Finish PCB
2025-02-10 Fix INA layout
2025-02-12 Add BOM+CPL
2025-02-12 Prepare to production (DFM ok)
2025-02-14 Add Documentation and minor tweaks
2025-02-14 Remove boardhouse designators
2025-02-14 Do file cleanup
2025-02-23 Add readme v1.md
2025-02-23 Fix typo
2025-02-23 Fix formatting
2025-02-24 Add license and render
2025-03-06 Edit typo
2026-02-10 Update project status in README
    Updated project status to reflect completion of bringup and testing.
